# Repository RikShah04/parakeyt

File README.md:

# parakeyt-docs
Ergonomic keyboard generator — PCB, firmware, and case file generation

# structure

## `reference-design/`
contains a completed reference design to act as a testing platform and schematic example of a potential parakeyt board.

it is hand designed, placed, and routed. it is not an actual output of the parakeyt toolchain.

# attribution
Footprints, models, symbols:
- RP2040-zero from https://github.com/crides/kleeb/ (MIT License)
- TLC59108IRGYR from manufacturer
- TLA2528IRTER from manufacturer
- AH49FNTR-G1 from manufacturer

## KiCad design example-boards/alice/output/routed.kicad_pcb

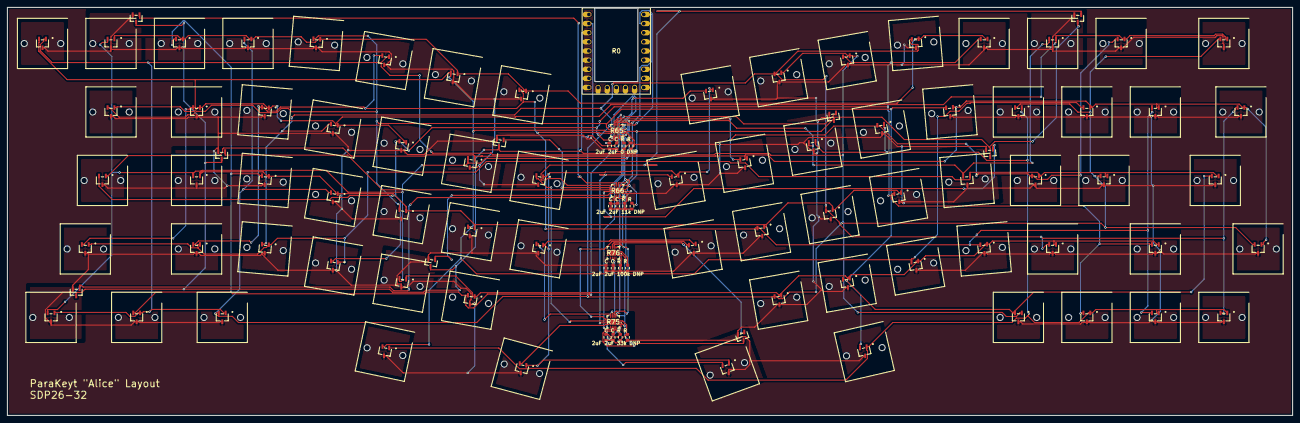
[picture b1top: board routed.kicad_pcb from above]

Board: 2 copper layers, 357.5 x 113.5 mm, 76 parts (0 on the bottom side), 43 nets.

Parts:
R0: rp2040-zero-tht
R1, R9, R17, R25, R33, R41, R49, R57, R67: SC59_DIO_KeyswitchOutline_NoRuleArea_mosfet
R2, R3, R4, R5, R6, R7, R8, R10, R11, R12, R13, R14, R15, R16, R18, R19, R20, R21, R22, R23, R24, R26, R27, R28, R29, R30, R31, R32, R34, R35, R36, R37, R38, R39, R40, R42, R43, R44, R45, R46, R47, R48, R50, R51, R52, R53, R54, R55, R56, R58, R59, R60, R61, R62, R63, R64, R68, R69, R70, R71, R72, R74: SC59_DIO_KeyswitchOutline_NoRuleArea_mosfet; SC59_DIO_KeyswitchOutline_NoRuleArea
R65, R66, R75, R76: WQFN16_RTE_TEX_with_caps_and_Rs

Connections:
+3.3v: R0.21, R1.6, R9.6, R17.6, R25.6, R33.6, R41.6, R49.6, R57.6, R65.7, R65.10, R65.20, R66.7, R66.10, R67.6, R75.7, R75.10, R75.20, R76.7, R76.10
GND: R0.22, R1.3, R1.5, R2.3, R3.3, R4.3, R5.3, R6.3, R7.3, R8.3, R9.3, R9.5, R10.3, R11.3, R12.3, R13.3, R14.3, R15.3, R16.3, R17.3, R17.5, R18.3, R19.3, R20.3, R21.3, R22.3, R23.3, R24.3, R25.3, R25.5, R26.3, R27.3, R28.3, R29.3, R30.3, R31.3, R32.3, R33.3, R33.5, R34.3, R35.3, R36.3, R37.3, R38.3, R39.3, R40.3, R41.3, R41.5, R42.3, R43.3, R44.3, R45.3, R46.3, R47.3, R48.3, R49.3, R49.5, R50.3, R51.3, R52.3, R53.3, R54.3, R55.3, R56.3, R57.3, R57.5, R58.3, R59.3, R60.3, R61.3, R62.3, R63.3, R64.3, R65.9, R65.17, R65.19, R65.23, R66.9, R66.17, R66.18, R66.19, R66.20, R66.21, R66.22, R66.23, R67.3, R67.5, R68.3, R69.3, R70.3, R71.3, R72.3, R74.3, R75.9, R75.17, R75.19, R75.23, R76.9, R76.17, R76.18, R76.19, R76.20, R76.21, R76.22, R76.23
SCL: R0.2, R65.13, R66.13, R75.13, R76.13
SDA: R0.1, R65.14, R66.14, R75.14, R76.14
addr10: R65.11, R65.21, R65.24
addr11: R75.11, R75.21, R75.24
addr20: R66.11, R66.24
addr21: R76.11, R76.24
decap10: R65.8, R65.18, R65.22
decap11: R75.8, R75.18, R75.22
m0c0: R1.2, R9.2, R17.2, R25.2, R33.2, R41.2, R49.2, R57.2, R65.15
m0c1: R2.2, R10.2, R18.2, R26.2, R34.2, R42.2, R50.2, R58.2, R65.16
m0c2: R3.2, R11.2, R19.2, R27.2, R35.2, R43.2, R51.2, R59.2, R65.1
m0c3: R4.2, R12.2, R20.2, R28.2, R36.2, R44.2, R52.2, R60.2, R65.2
m0c4: R5.2, R13.2, R21.2, R29.2, R37.2, R45.2, R53.2, R61.2, R65.3
m0c5: R6.2, R14.2, R22.2, R30.2, R38.2, R46.2, R54.2, R62.2, R65.4
m0c6: R7.2, R15.2, R23.2, R31.2, R39.2, R47.2, R55.2, R63.2, R65.5
m0c7: R8.2, R16.2, R24.2, R32.2, R40.2, R48.2, R56.2, R64.2, R65.6
m0r0: R1.4, R66.15
m0r0MOS: R1.1, R2.1, R3.1, R4.1, R5.1, R6.1, R7.1, R8.1
m0r1: R9.4, R66.16
m0r1MOS: R9.1, R10.1, R11.1, R12.1, R13.1, R14.1, R15.1, R16.1
m0r2: R17.4, R66.1
m0r2MOS: R17.1, R18.1, R19.1, R20.1, R21.1, R22.1, R23.1, R24.1
m0r3: R25.4, R66.2
m0r3MOS: R25.1, R26.1, R27.1, R28.1, R29.1, R30.1, R31.1, R32.1
m0r4: R33.4, R66.3
m0r4MOS: R33.1, R34.1, R35.1, R36.1, R37.1, R38.1, R39.1, R40.1
m0r5: R41.4, R66.4
m0r5MOS: R41.1, R42.1, R43.1, R44.1, R45.1, R46.1, R47.1, R48.1
m0r6: R49.4, R66.5
m0r6MOS: R49.1, R50.1, R51.1, R52.1, R53.1, R54.1, R55.1, R56.1
m0r7: R57.4, R66.6
m0r7MOS: R57.1, R58.1, R59.1, R60.1, R61.1, R62.1, R63.1, R64.1
m1c0: R67.2, R75.15
m1c1: R68.2, R75.16
m1c2: R69.2, R75.1
m1c3: R70.2, R75.2
m1c4: R71.2, R75.3
m1c5: R72.2, R75.4
m1c7: R74.2, R75.6
m1r0: R67.4, R76.15
m1r0MOS: R67.1, R68.1, R69.1, R70.1, R71.1, R72.1, R74.1

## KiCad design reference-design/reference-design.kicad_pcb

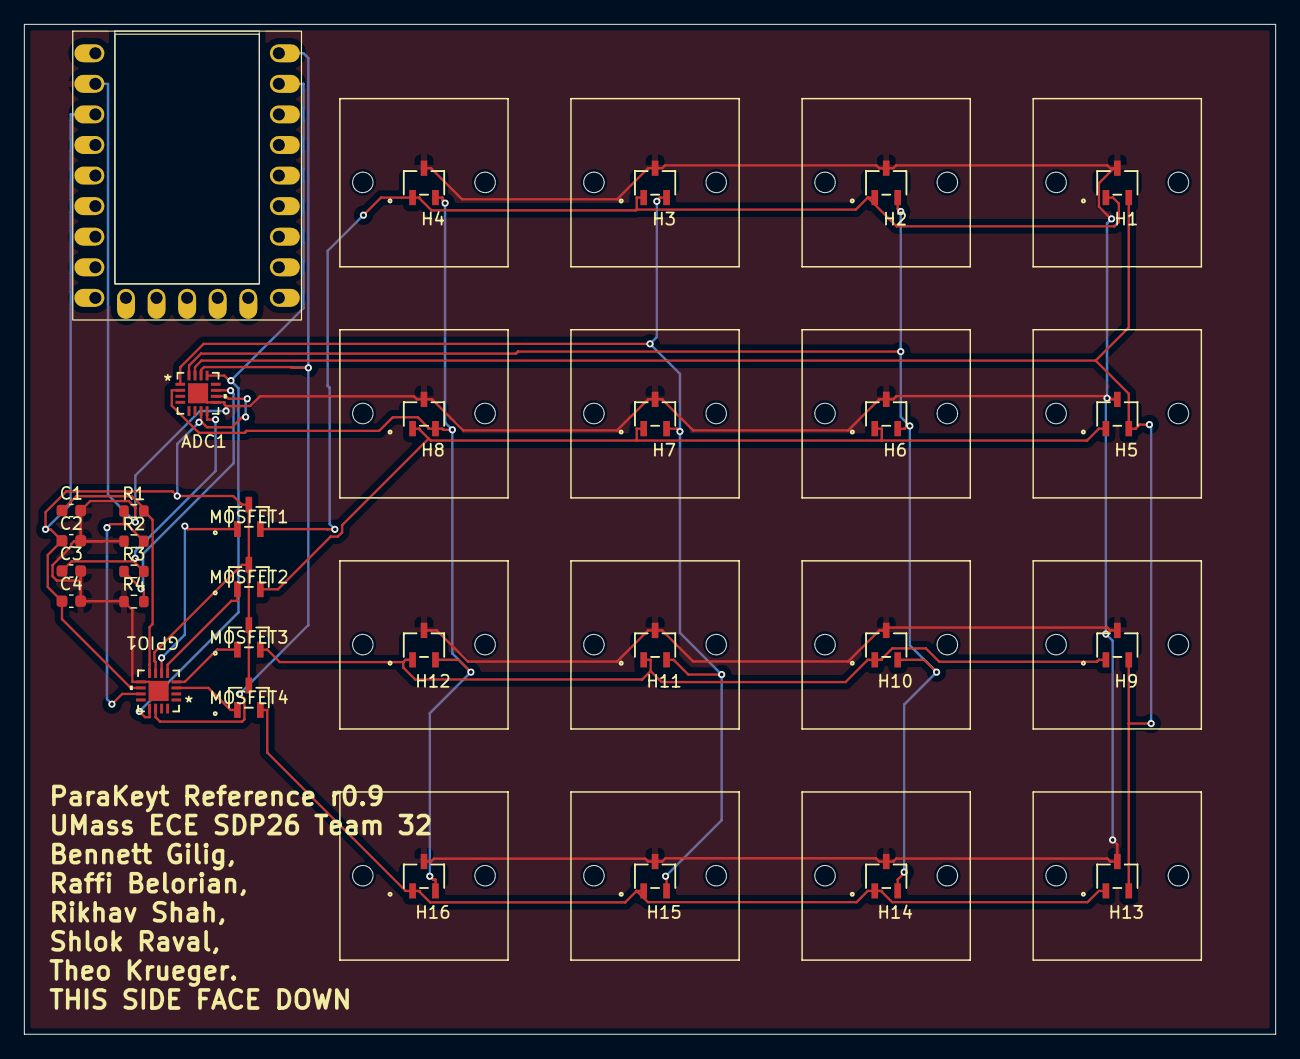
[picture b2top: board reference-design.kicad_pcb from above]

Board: 2 copper layers, 104.0 x 83.9 mm, 31 parts (0 on the bottom side), 20 nets.

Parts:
ADC1: TLA2528IRTER; WQFN16_RTE_TEX
C1, C2, C3, C4: 2uF; C_0603_1608Metric
GPIO1: TLA2528IRTER; WQFN16_RTE_TEX
H1, H2, H3, H4, H5, H6, H7, H8, H9, H10, H11, H12, H13, H14, H15, H16: AH49FNTR-G1; SC59_DIO_KeyswitchOutline_NoRuleArea
MCU1: RP2040-Zero; rp2040-zero-tht
MOSFET1, MOSFET2, MOSFET3, MOSFET4: SI2342DS-T1-GE3; SOT-23_TO-236_VIS
R1: 11K; R_0603_1608Metric
R2, R4: DNP; R_0603_1608Metric
R3: 0; R_0603_1608Metric

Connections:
+3.3V: ADC1.7 (AVDD), ADC1.10 (DVDD), C2.1, C4.1, GPIO1.7 (AVDD), GPIO1.10 (DVDD), MCU1.21 (3V3), MOSFET1.3 (D), MOSFET2.3 (D), MOSFET3.3 (D), MOSFET4.3 (D)
GND: ADC1.9 (GND), ADC1.17 (GND), C1.2, C2.2, C3.2, C4.2, GPIO1.9 (GND), GPIO1.17 (GND), H1.3 (GND), H2.3 (GND), H3.3 (GND), H4.3 (GND), H5.3 (GND), H6.3 (GND), H7.3 (GND), H8.3 (GND), H9.3 (GND), H10.3 (GND), H11.3 (GND), H12.3 (GND), H13.3 (GND), H14.3 (GND), H15.3 (GND), H16.3 (GND), MCU1.22 (GND), R2.1, R4.1
unnamed: ADC1.11 (ADDR), R3.1, R4.2
unnamed: ADC1.8 (DECAP), C3.1, R3.2
unnamed: GPIO1.11 (ADDR), R1.1, R2.2
unnamed: C1.1, GPIO1.8 (DECAP), R1.2
unnamed: H1.1 (VCC), H2.1 (VCC), H3.1 (VCC), H4.1 (VCC), MOSFET1.2 (S)
unnamed: H5.1 (VCC), H6.1 (VCC), H7.1 (VCC), H8.1 (VCC), MOSFET2.2 (S)
unnamed: H9.1 (VCC), H10.1 (VCC), H11.1 (VCC), H12.1 (VCC), MOSFET3.2 (S)
unnamed: H13.1 (VCC), H14.1 (VCC), H15.1 (VCC), H16.1 (VCC), MOSFET4.2 (S)
col0: ADC1.15 (AIN0/GPIO0), H1.2 (OUT), H5.2 (OUT), H9.2 (OUT), H13.2 (OUT)
col1: ADC1.16 (AIN1/GPIO1), H2.2 (OUT), H6.2 (OUT), H10.2 (OUT), H14.2 (OUT)
col2: ADC1.1 (AIN2/GPIO2), H3.2 (OUT), H7.2 (OUT), H11.2 (OUT), H15.2 (OUT)
col3: ADC1.2 (AIN3/GPIO3), H4.2 (OUT), H8.2 (OUT), H12.2 (OUT), H16.2 (OUT)
i2c0_scl: ADC1.13 (SCL), GPIO1.13 (SCL), MCU1.2 (1)
i2c0_sda: ADC1.14 (SDA), GPIO1.14 (SDA), MCU1.1 (0)
row0: GPIO1.6 (AIN7/GPIO7), MOSFET1.1 (G)
row1: GPIO1.5 (AIN6/GPIO6), MOSFET2.1 (G)
row2: GPIO1.4 (AIN5/GPIO5), MOSFET3.1 (G)
row3: GPIO1.3 (AIN4/GPIO4), MOSFET4.1 (G)

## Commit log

2026-01-22 reference design PCBs unrouted
    needed for testing autorouter
2026-02-17 replace led driver with another ADC (to be used as gpio to drive MOSFETs)
2026-02-17 add rp2040 cutout and keyswitch outlines
2026-02-19 why was this file here oopsies
2026-02-19 stfupdate
2026-02-24 prep for order
2026-04-01 config -> generated config for 4x4
2026-04-01 pipeline push
2026-04-02 more progress, pipeline almost working
2026-04-02 disabled headless mode for routing
2026-04-02 webui helper script
2026-04-02 better pipeline
2026-04-02 key fix
2026-04-02 pipeilne working minus route
2026-04-05 pipeline shtuff
2026-04-06 good pipeline script fixes
2026-04-06 parameterize pipeline WIP
2026-04-06 oneliner script worky
2026-04-09 tkl config
2026-04-09 new ex layouts
2026-04-09 sdvx2
2026-04-13 arg in pipeline
2026-04-13 fix some shi
2026-04-21 lots of stuff
2026-04-28 modified pipeline to work on loonix (hopefully)
2026-05-01 changed a bunch of things and stuff
2026-05-01 fwgen hotfix
2026-05-01 fixed default alice issue
